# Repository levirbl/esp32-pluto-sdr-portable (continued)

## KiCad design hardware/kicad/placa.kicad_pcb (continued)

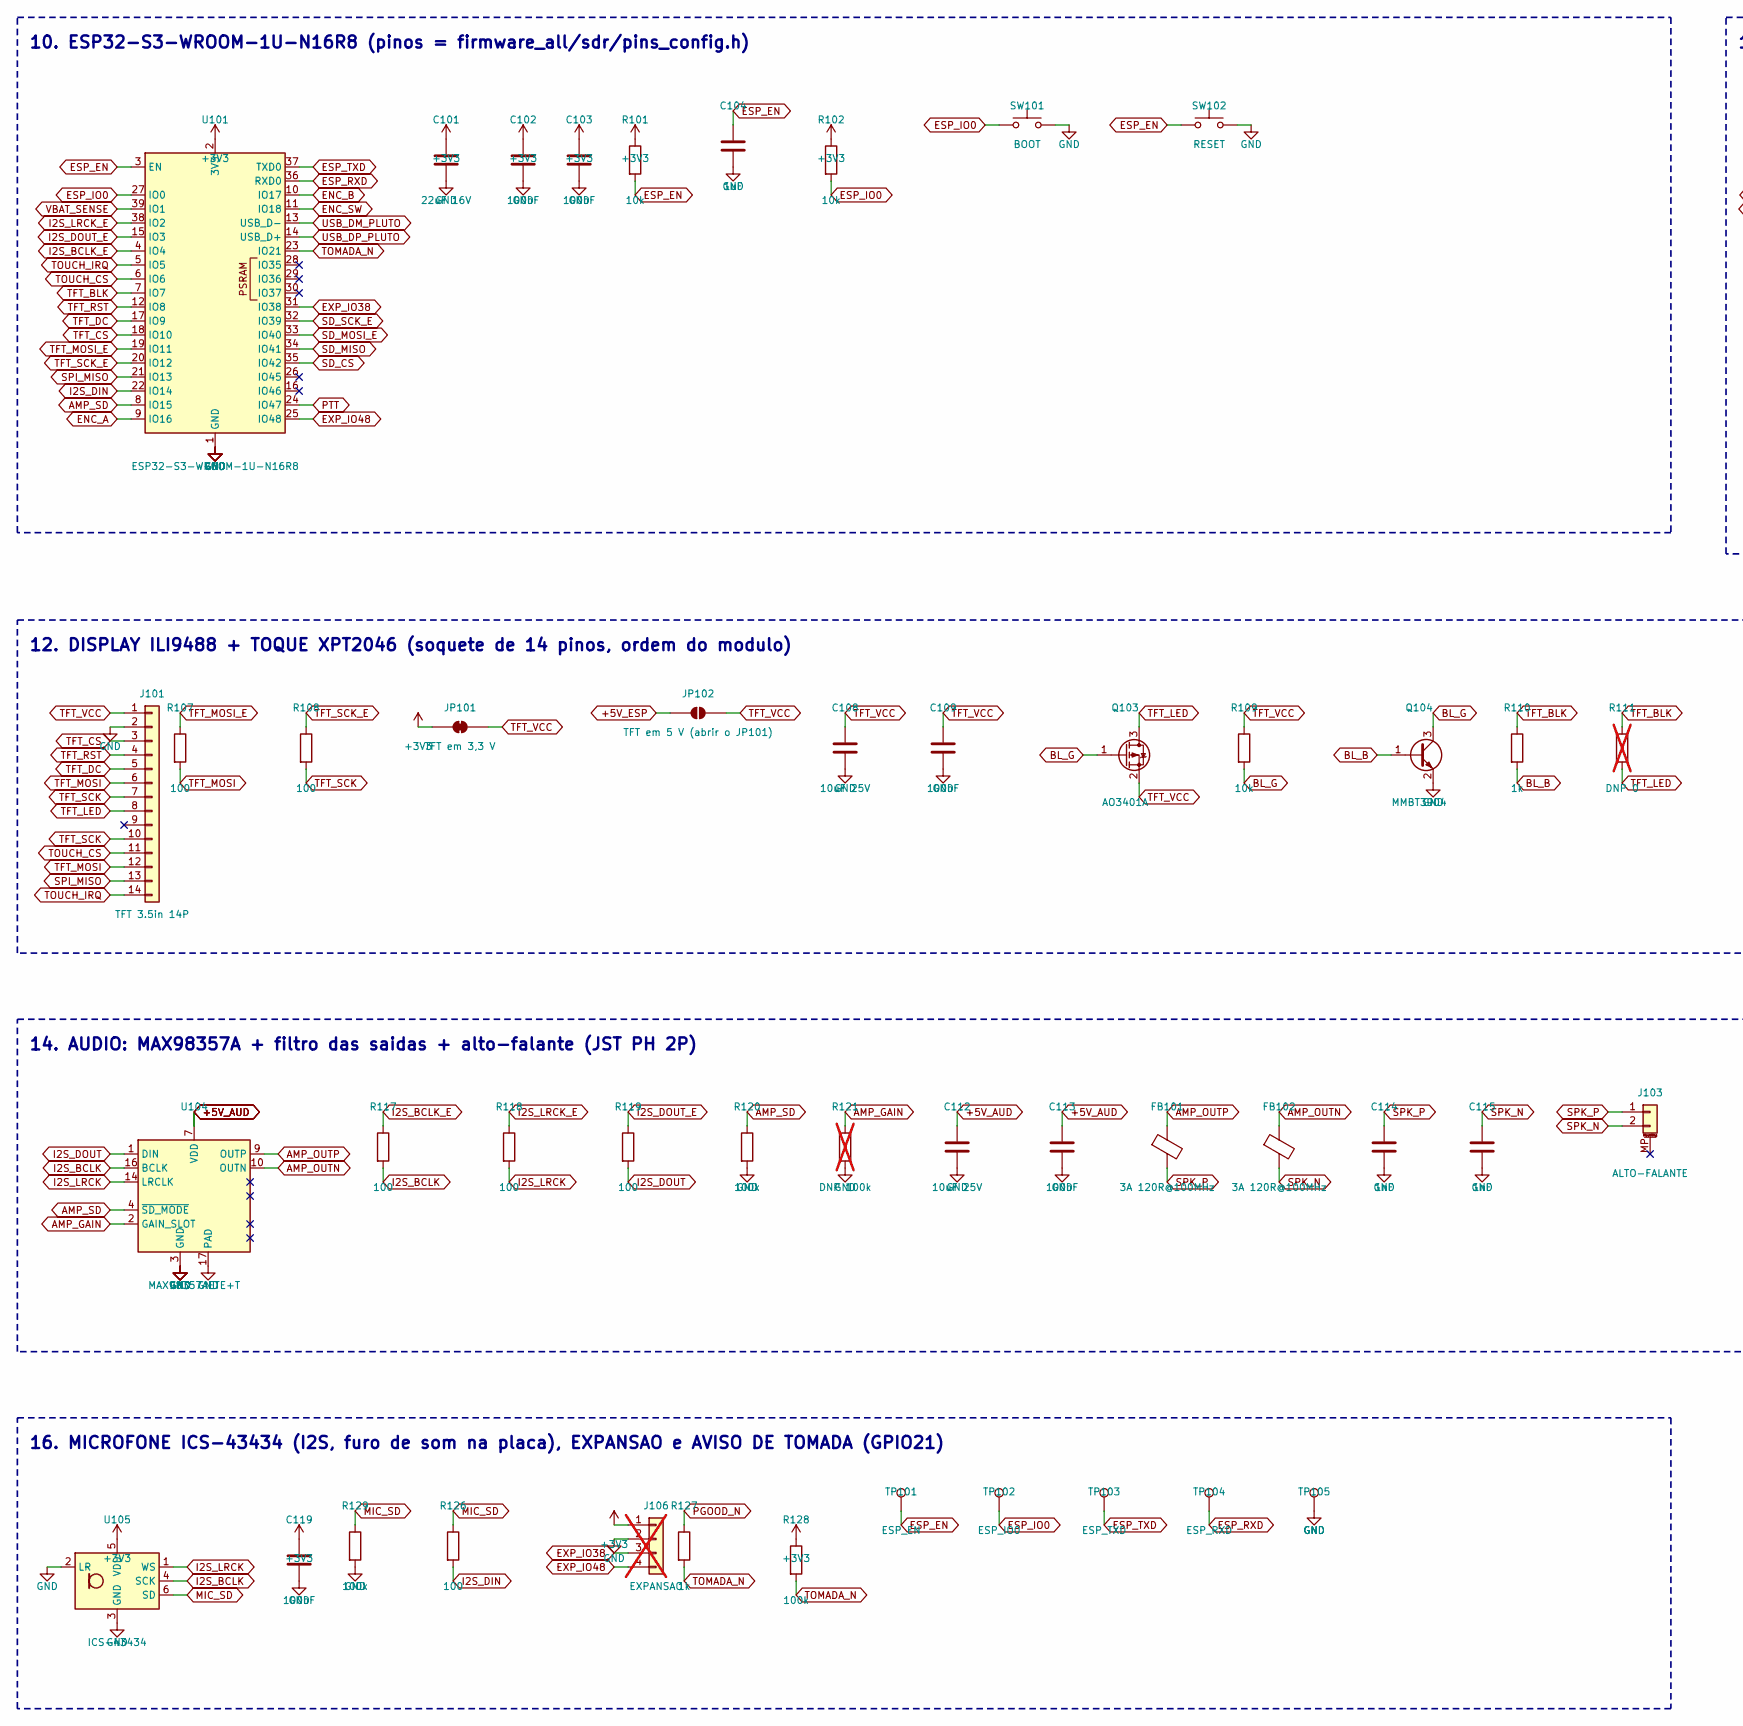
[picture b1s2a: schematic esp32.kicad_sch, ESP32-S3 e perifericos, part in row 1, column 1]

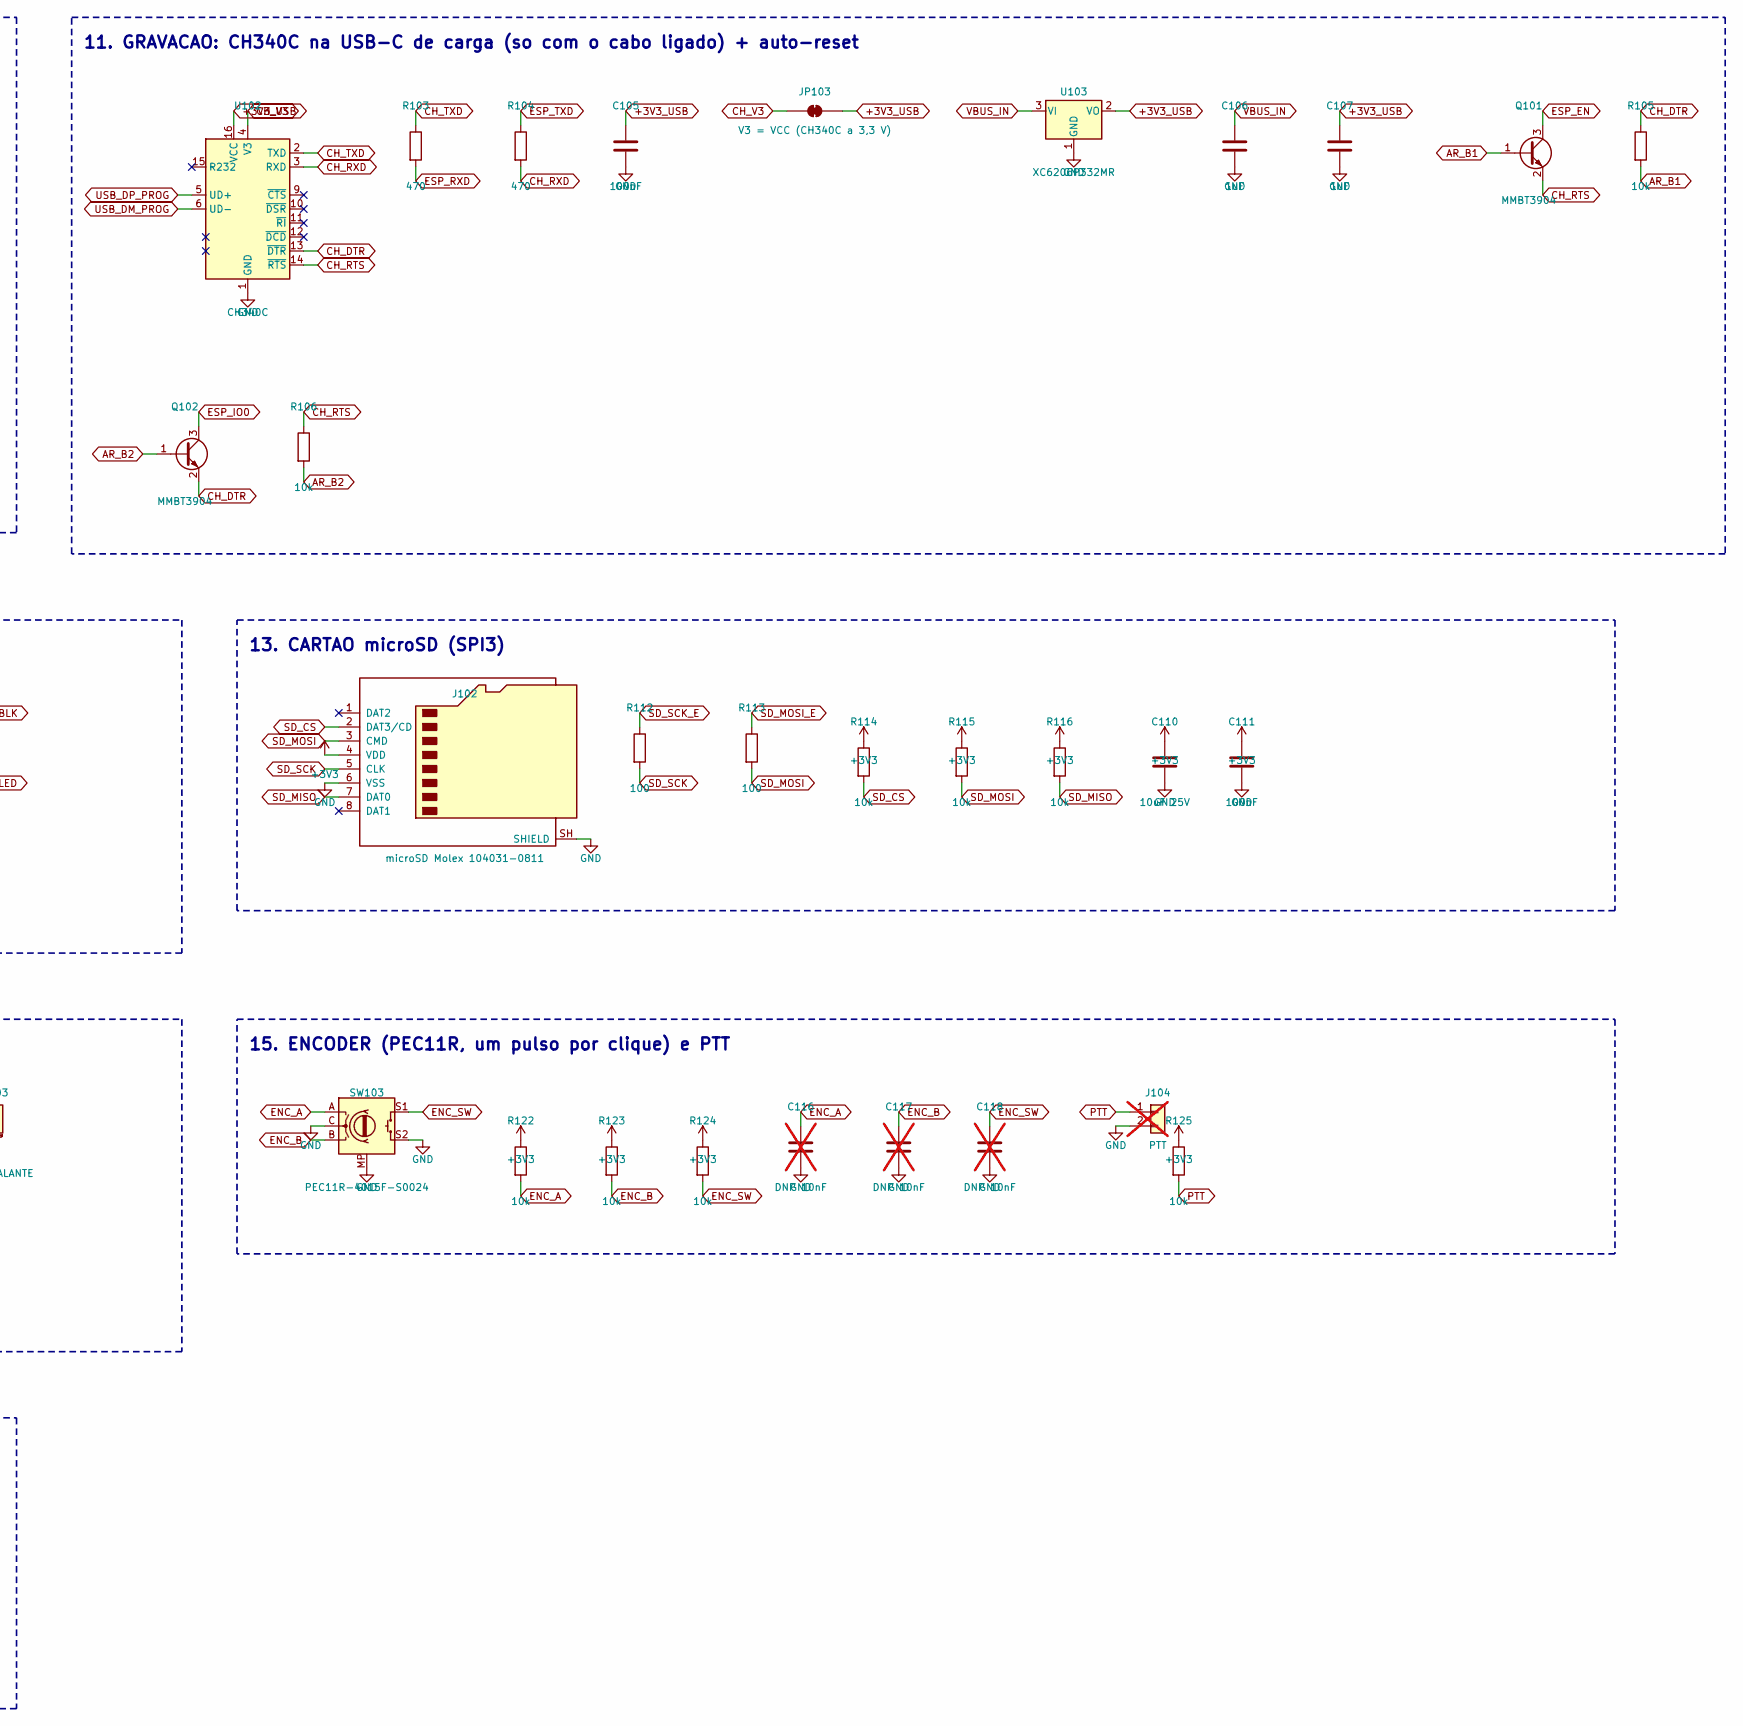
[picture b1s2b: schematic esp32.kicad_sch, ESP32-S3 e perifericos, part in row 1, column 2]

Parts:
C101: 22uF 16V; C_1206_3216Metric; LCSC C90146
C102, C103, C105, C109, C111, C113, C119: 100nF; C_0603_1608Metric; LCSC C14663
C104, C106, C107: 1uF; C_0603_1608Metric; LCSC C15849
C108, C110, C112: 10uF 25V; C_0805_2012Metric; LCSC C15850
C114, C115: 1nF; C_0603_1608Metric; LCSC C1588
C116, C117, C118: DNP 10nF; C_0603_1608Metric; LCSC C57112; not fitted
FB101, FB102: 3A 120R@100MHz; L_1206_3216Metric; LCSC C139197
J101: TFT 3.5in 14P; PinSocket_1x14_P2.54mm_Vertical
J102: microSD Molex 104031-0811; microSD_HC_Molex_104031-0811; LCSC C585350
J103: ALTO-FALANTE; JST_PH_S2B-PH-SM4-TB_1x02-1MP_P2.00mm_Horizontal; LCSC C54582899
J104: PTT; PinHeader_1x02_P2.54mm_Vertical; not fitted
J106: EXPANSAO; PinHeader_1x04_P2.54mm_Vertical; not fitted
JP101: TFT em 3,3 V; SolderJumper-2_P1.3mm_Bridged2Bar_RoundedPad1.0x1.5mm
JP102: TFT em 5 V (abrir o JP101); SolderJumper-2_P1.3mm_Open_RoundedPad1.0x1.5mm
JP103: V3 = VCC (CH340C a 3,3 V); SolderJumper-2_P1.3mm_Bridged2Bar_RoundedPad1.0x1.5mm
Q101, Q102, Q104: MMBT3904; SOT-23; LCSC C20526
Q103: AO3401A; SOT-23; LCSC C15127
R101, R102, R105, R106, R109, R114, R115, R116, R122, R123, R124, R125: 10k; R_0603_1608Metric; LCSC C25804
R103, R104: 470; R_0603_1608Metric; LCSC C23179
R107, R108, R112, R113, R117, R118, R119, R126: 100; R_0603_1608Metric; LCSC C22775
R110, R127: 1k; R_0603_1608Metric; LCSC C21190
R111: DNP 0; R_0603_1608Metric; LCSC C21189; not fitted
R120, R128, R129: 100k; R_0603_1608Metric; LCSC C25803
R121: DNP 100k; R_0603_1608Metric; LCSC C25803; not fitted
SW101: BOOT; SW_Push_1P1T_XKB_TS-1187A; LCSC C318889
SW102: RESET; SW_Push_1P1T_XKB_TS-1187A; LCSC C318889
SW103: PEC11R-4015F-S0024; RotaryEncoder_Bourns_PEC11R-4xxxF-S; LCSC C143789
TP101: ESP_EN; TestPoint_Pad_D1.5mm
TP102: ESP_IO0; TestPoint_Pad_D1.5mm
TP103: ESP_TXD; TestPoint_Pad_D1.5mm
TP104: ESP_RXD; TestPoint_Pad_D1.5mm
TP105: GND; TestPoint_Pad_D1.5mm
U101: ESP32-S3-WROOM-1U-N16R8; ESP32-S3-WROOM-1U; LCSC C3013946
U102: CH340C; SOIC-16_3.9x9.9mm_P1.27mm; LCSC C84681
U103: XC6206P332MR; SOT-23-3; LCSC C347376
U104: MAX98357AETE+T; TQFN-16-1EP_3x3mm_P0.5mm_EP1.23x1.23mm; LCSC C910544
U105: ICS-43434; InvenSense_ICS-43434-6_3.5x2.65mm; LCSC C5656610

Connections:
+3V3: C101.1, C102.1, C103.1, C110.1, C111.1, C119.1, J102.4 (VDD), J106.1, JP101.1 (A), R101.1, R102.1, R114.1, R115.1, R116.1, R122.1, R123.1, R124.1, R125.1, R128.1, U101.2 (3V3), U105.5 (VDD); also elsewhere on the board
+3V3_USB: C105.1, C107.1, JP103.2 (B), U102.16 (VCC), U103.2 (VO)
+5V_AUD: C112.1, C113.1, U104.7 (VDD), U104.8 (VDD); also elsewhere on the board
+5V_ESP: JP102.1 (A); also elsewhere on the board
AMP_GAIN: R121.1, U104.2 (GAIN_SLOT)
AMP_OUTN: FB102.1, U104.10 (OUTN)
AMP_OUTP: FB101.1, U104.9 (OUTP)
AMP_SD: R120.1, U101.8 (IO15), U104.4 (~SD_MODE)
AR_B1: Q101.1 (B), R105.2
AR_B2: Q102.1 (B), R106.2
BL_B: Q104.1 (B), R110.2
BL_G: Q103.1 (G), Q104.3 (C), R109.2
CH_DTR: Q102.2 (E), R105.1, U102.13 (~DTR)
CH_RTS: Q101.2 (E), R106.1, U102.14 (~RTS)
CH_RXD: R104.2, U102.3 (RXD)
CH_TXD: R103.1, U102.2 (TXD)
CH_V3: JP103.1 (A), U102.4 (V3)
ENC_A: C116.1, R122.2, SW103.A, U101.9 (IO16)
ENC_B: C117.1, R123.2, SW103.B, U101.10 (IO17)
ENC_SW: C118.1, R124.2, SW103.S1, U101.11 (IO18)
ESP_EN: C104.1, Q101.3 (C), R101.2, SW102.1, TP101.1, U101.3 (EN)
ESP_IO0: Q102.3 (C), R102.2, SW101.1, TP102.1, U101.27 (IO0)
ESP_RXD: R103.2, TP104.1, U101.36 (RXD0)
ESP_TXD: R104.1, TP103.1, U101.37 (TXD0)
EXP_IO38: J106.3, U101.31 (IO38)
EXP_IO48: J106.4, U101.25 (IO48)
GND: C101.2, C102.2, C103.2, C104.2, C105.2, C106.2, C107.2, C108.2, C109.2, C110.2, C111.2, C112.2, C113.2, C114.2, C115.2, C116.2, C117.2, C118.2, C119.2, J101.2, J102.6 (VSS), J102.SH (SHIELD), J104.2, J106.2, Q104.2 (E), R120.2, R121.2, R129.2, SW101.2, SW102.2, SW103.C, SW103.MP, SW103.S2, TP105.1, U101.1 (GND), U101.40 (GND), U101.41 (GND), U102.1 (GND), U103.1 (GND), U104.3 (GND), U104.11 (GND), U104.15 (GND), U104.17 (PAD), U105.2 (LR), U105.3 (GND); also elsewhere on the board
I2S_BCLK: R117.2, U104.16 (BCLK), U105.4 (SCK)
I2S_BCLK_E: R117.1, U101.4 (IO4)
I2S_DIN: R126.2, U101.22 (IO14)
I2S_DOUT: R119.2, U104.1 (DIN)
I2S_DOUT_E: R119.1, U101.15 (IO3)
I2S_LRCK: R118.2, U104.14 (LRCLK), U105.1 (WS)
I2S_LRCK_E: R118.1, U101.38 (IO2)
MIC_SD: R126.1, R129.1, U105.6 (SD)
PGOOD_N: R127.1; also elsewhere on the board
PTT: J104.1, R125.2, U101.24 (IO47)
SD_CS: J102.2 (DAT3/CD), R114.2, U101.35 (IO42)
SD_MISO: J102.7 (DAT0), R116.2, U101.34 (IO41)
SD_MOSI: J102.3 (CMD), R113.2, R115.2
SD_MOSI_E: R113.1, U101.33 (IO40)
SD_SCK: J102.5 (CLK), R112.2
SD_SCK_E: R112.1, U101.32 (IO39)
SPI_MISO: J101.13, U101.21 (IO13)
SPK_N: C115.1, FB102.2, J103.2
SPK_P: C114.1, FB101.2, J103.1
TFT_BLK: R110.1, R111.1, U101.7 (IO7)
TFT_CS: J101.3, U101.18 (IO10)
TFT_DC: J101.5, U101.17 (IO9)
TFT_LED: J101.8, Q103.3 (D), R111.2
TFT_MOSI: J101.6, J101.12, R107.2
TFT_MOSI_E: R107.1, U101.19 (IO11)
TFT_RST: J101.4, U101.12 (IO8)
TFT_SCK: J101.7, J101.10, R108.2
TFT_SCK_E: R108.1, U101.20 (IO12)
TFT_VCC: C108.1, C109.1, J101.1, JP101.2 (B), JP102.2 (B), Q103.2 (S), R109.1
TOMADA_N: R127.2, R128.2, U101.23 (IO21)
TOUCH_CS: J101.11, U101.6 (IO6)
TOUCH_IRQ: J101.14, U101.5 (IO5)
USB_DM_PLUTO: U101.13 (USB_D-); also elsewhere on the board
USB_DM_PROG: U102.6 (UD-); also elsewhere on the board
USB_DP_PLUTO: U101.14 (USB_D+); also elsewhere on the board
USB_DP_PROG: U102.5 (UD+); also elsewhere on the board
VBAT_SENSE: U101.39 (IO1); also elsewhere on the board
VBUS_IN: C106.1, U103.3 (VI); also elsewhere on the board

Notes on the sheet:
10. ESP32-S3-WROOM-1U-N16R8 (pinos = firmware_all/sdr/pins_config.h)
11. GRAVACAO: CH340C na USB-C de carga (so com o cabo ligado) + auto-reset
12. DISPLAY ILI9488 + TOQUE XPT2046 (soquete de 14 pinos, ordem do modulo)
13. CARTAO microSD (SPI3)
14. AUDIO: MAX98357A + filtro das saidas + alto-falante (JST PH 2P)
15. ENCODER (PEC11R, um pulso por clique) e PTT
16. MICROFONE ICS-43434 (I2S, furo de som na placa), EXPANSAO e AVISO DE TOMADA (GPIO21)

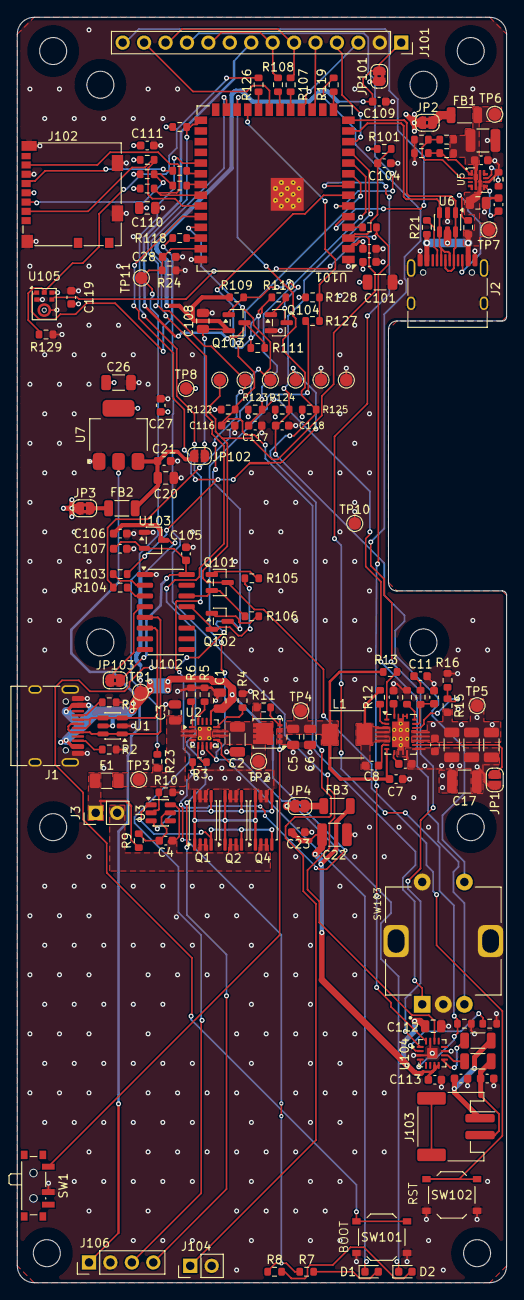
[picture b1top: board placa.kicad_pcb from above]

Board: 4 copper layers, 58.0 x 150.0 mm, 176 parts (0 on the bottom side), 108 nets.

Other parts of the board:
H1, H2, H3, H4, H5, H6, H7, H8, H9, H10: M3; MountingHole_3.2mm_M3

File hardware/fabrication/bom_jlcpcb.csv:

Comment,Designator,Footprint,LCSC Part #,Quantity
4.7uF 25V,C1,C_0805_2012Metric,C1779,1
47nF,C10,C_0603_1608Metric,C1622,1
1uF,"C104,C106,C107",C_0603_1608Metric,C15849,3
3.9nF,C11,C_0603_1608Metric,C309474,1
1nF,"C114,C115",C_0603_1608Metric,C1588,2
100uF 10V,"C17,C18,C22",C_1210_3225Metric,C23742,3
22uF 16V,"C2,C13,C14,C15,C26,C101",C_1206_3216Metric,C90146,6
22nF,C24,C_0603_1608Metric,C21122,1
10uF 25V,"C3,C5,C6,C20,C25,C108,C110,C112",C_0805_2012Metric,C15850,8
100nF,"C4,C7,C8,C16,C19,C21,C23,C27,C28,C102,C103,C105,C109,C111,C113,C119",C_0603_1608Metric,C14663,16
2.2uF,C9,C_0603_1608Metric,C23630,1
vermelho CARGA,D1,LED_0603_1608Metric,C2286,1
verde TOMADA,D2,LED_0603_1608Metric,C12624,1
7A,F1,Fuse_1206_3216Metric,C183154,1
6A 75R@100MHz,FB1,L_1206_3216Metric,C2661688,1
3A 120R@100MHz,"FB2,FB3,FB101,FB102",L_1206_3216Metric,C139197,4
USB-C carga/gravar,J1,USB_C_Receptacle_HRO_TYPE-C-31-M-12,C165948,1
microSD Molex 104031-0811,J102,microSD_HC_Molex_104031-0811,C585350,1
ALTO-FALANTE,J103,JST_PH_S2B-PH-SM4-TB_1x02-1MP_P2.00mm_Horizontal,C54582899,1
USB-C PLUTO (host),J2,USB_C_Receptacle_HRO_TYPE-C-31-M-12,C165948,1
1.0uH MWSA0503S,L1,L_Sunlord_MWSA0503S,C408355,1
8205A,"Q1,Q2",TSSOP-8_4.4x3mm_P0.65mm,C5148694,2
MMBT3904,"Q101,Q102,Q104",SOT-23,C20526,3
AO3401A,Q103,SOT-23,C15127,1
CSD25402Q3A,Q3,VSON-8_3.3x3.3mm_P0.65mm_NexFET,C111356,1
5.1k,"R1,R2",R_0603_1608Metric,C23186,2
1k,"R10,R110,R127",R_0603_1608Metric,C21190,3
470,"R103,R104",R_0603_1608Metric,C23179,2
100k,"R11,R13,R120,R129,R128",R_0603_1608Metric,C25803,5
150k 1%,R12,R_0603_1608Metric,C22807,1
180k 1%,"R14,R15",R_0603_1608Metric,C22827,2
56k 1%,"R16,R18,R25",R_0603_1608Metric,C23206,3
20k 1%,"R17,R19",R_0603_1608Metric,C4184,2
1.3k 1%,R20,R_0603_1608Metric,C22767,1
56k,"R21,R22",R_0603_1608Metric,C23206,2
300k 1%,R23,R_0603_1608Metric,C23024,1
100k 1%,R24,R_0603_1608Metric,C25803,1
15k 1%,R26,R_0603_1608Metric,C22809,1
10k,"R3,R6,R101,R102,R105,R106,R109,R114,R115,R116,R122,R123,R124,R125",R_0603_1608Metric,C25804,14
1.1k 1%,R4,R_0603_1608Metric,C137780,1
1k 1%,R5,R_0603_1608Metric,C21190,1
1.5k,"R7,R8",R_0603_1608Metric,C22843,2
100,"R9,R107,R108,R112,R113,R117,R118,R119,R126",R_0603_1608Metric,C22775,9
LIGA/DESLIGA,SW1,SW_SPDT_PCM12,C221841,1
BOOT,SW101,SW_Push_1P1T_XKB_TS-1187A,C318889,1
RESET,SW102,SW_Push_1P1T_XKB_TS-1187A,C318889,1
USBLC6-2SC6,"U1,U6",SOT-23-6,C2969755,2
ESP32-S3-WROOM-1U-N16R8,U101,ESP32-S3-WROOM-1U,C3013946,1
CH340C,U102,SOIC-16_3.9x9.9mm_P1.27mm,C84681,1
XC6206P332MR,U103,SOT-23-3,C347376,1
MAX98357AETE+T,U104,TQFN-16-1EP_3x3mm_P0.5mm_EP1.23x1.23mm,C910544,1
ICS-43434,U105,InvenSense_ICS-43434-6_3.5x2.65mm,C5656610,1
BQ24074RGTR,U2,VQFN-16-1EP_3x3mm_P0.5mm_EP1.6x1.6mm_ThermalVias,C54313,1
DW01A,U3,SOT-23-6,C42380662,1
TPS61088RHLR,U4,Texas_VQFN-RHL-20_ThermalVias,C87357,1
TPS259470ARPWR,U5,TI_RPW0010A,C3662799,1
AMS1117-3.3,U7,SOT-223-3_TabPin2,C6186,1
